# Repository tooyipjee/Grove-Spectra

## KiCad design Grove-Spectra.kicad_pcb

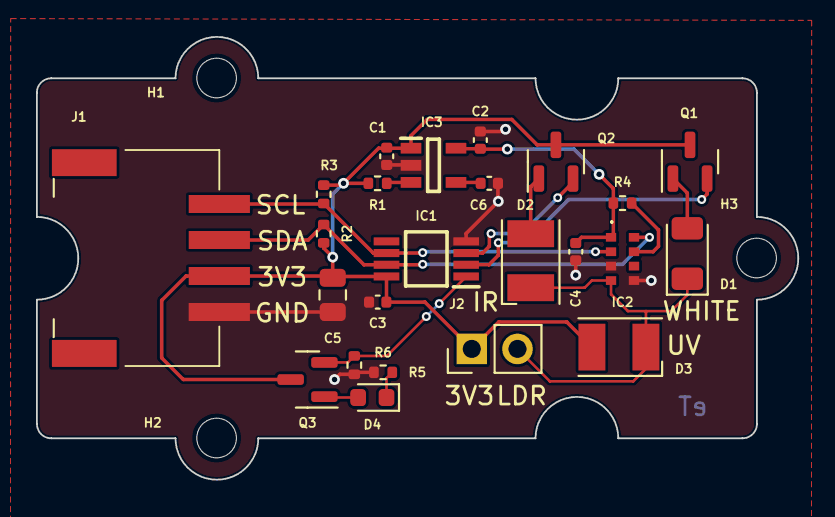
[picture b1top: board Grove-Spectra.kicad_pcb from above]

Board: 2 copper layers, 42.3 x 24.6 mm, 28 parts (1 on the bottom side), 16 nets.

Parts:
C1, C2, C3, C4, C6: 100n; C_0402_1005Metric
C5: 10u; C_0805_2012Metric
D1: WHITE 5000K; LED_1206_3216Metric
D2: IR_940NM; LED_PLCC-2
D3: UV_405NM; LED_PLCC-2
D4: Green_0603; LED_0603_1608Metric
FID1: Fiducial; Product Stamp
H1, H2, H3: MountingHole; MountingHole_2.2mm_M2
IC1: PCA9536DP,118; SOP65P490X110-8N
IC2: AS7341-DLGT; AS7343DLGM
IC3: SPX3819M5-L-1-8_TR; SOT95P280X145-5N
J1: 114020164
J2: Conn_01x02; PinHeader_1x02_P2.54mm_Vertical
Q1, Q2, Q3: BS250FTA; SOT-23
R1, R5: 1k; R_0402_1005Metric
R2, R3, R4, R6: 4.7k; R_0402_1005Metric

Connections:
+1V8: C2.1, C4.1, IC2.1 (VDD), IC3.5 (VOUT), R4.1
+3V3: C1.1, C3.1, C5.1, D3.2 (A), IC1.8 (VDD), IC3.1 (VIN), J1.3, J2.1, Q1.3 (S), Q2.3 (S), Q3.3 (S), R1.1, R2.1, R3.1
/GPIO_0: IC1.1 (IO0), Q3.2 (G), R6.1
/GPIO_1: IC1.2 (IO1), Q1.2 (G)
/GPIO_2: IC1.3 (IO2), Q2.2 (G)
/LDR: D1.1 (K), D2.1 (K), D3.1 (K), IC2.4 (LDR), J2.2
GND: C1.2, C2.2, C3.2, C4.2, C5.2, C6.2, IC1.4 (VSS), IC2.3 (GND), IC2.5 (PGND), IC3.2 (GND), J1.4, R5.2, R6.2
unnamed: C6.1, IC3.4 (ADJ/BYP)
unnamed: D1.2 (A), Q1.1 (D)
unnamed: D2.2 (A), Q2.1 (D)
unnamed: D4.1 (K), R5.1
unnamed: D4.2 (A), Q3.1 (D)
unnamed: IC2.7 (INT), R4.2
unnamed: IC3.3 (EN), R1.2
SCL: IC1.6 (SCL), IC2.2 (SCL), J1.1, R3.2
SDA: IC1.7 (SDA), IC2.8 (SDA), J1.2, R2.2

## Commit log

2022-11-15 Released for manufacture
2022-11-22 Updated for DFA
2022-11-23 Fixed for DA
2023-01-04 Created demo code
